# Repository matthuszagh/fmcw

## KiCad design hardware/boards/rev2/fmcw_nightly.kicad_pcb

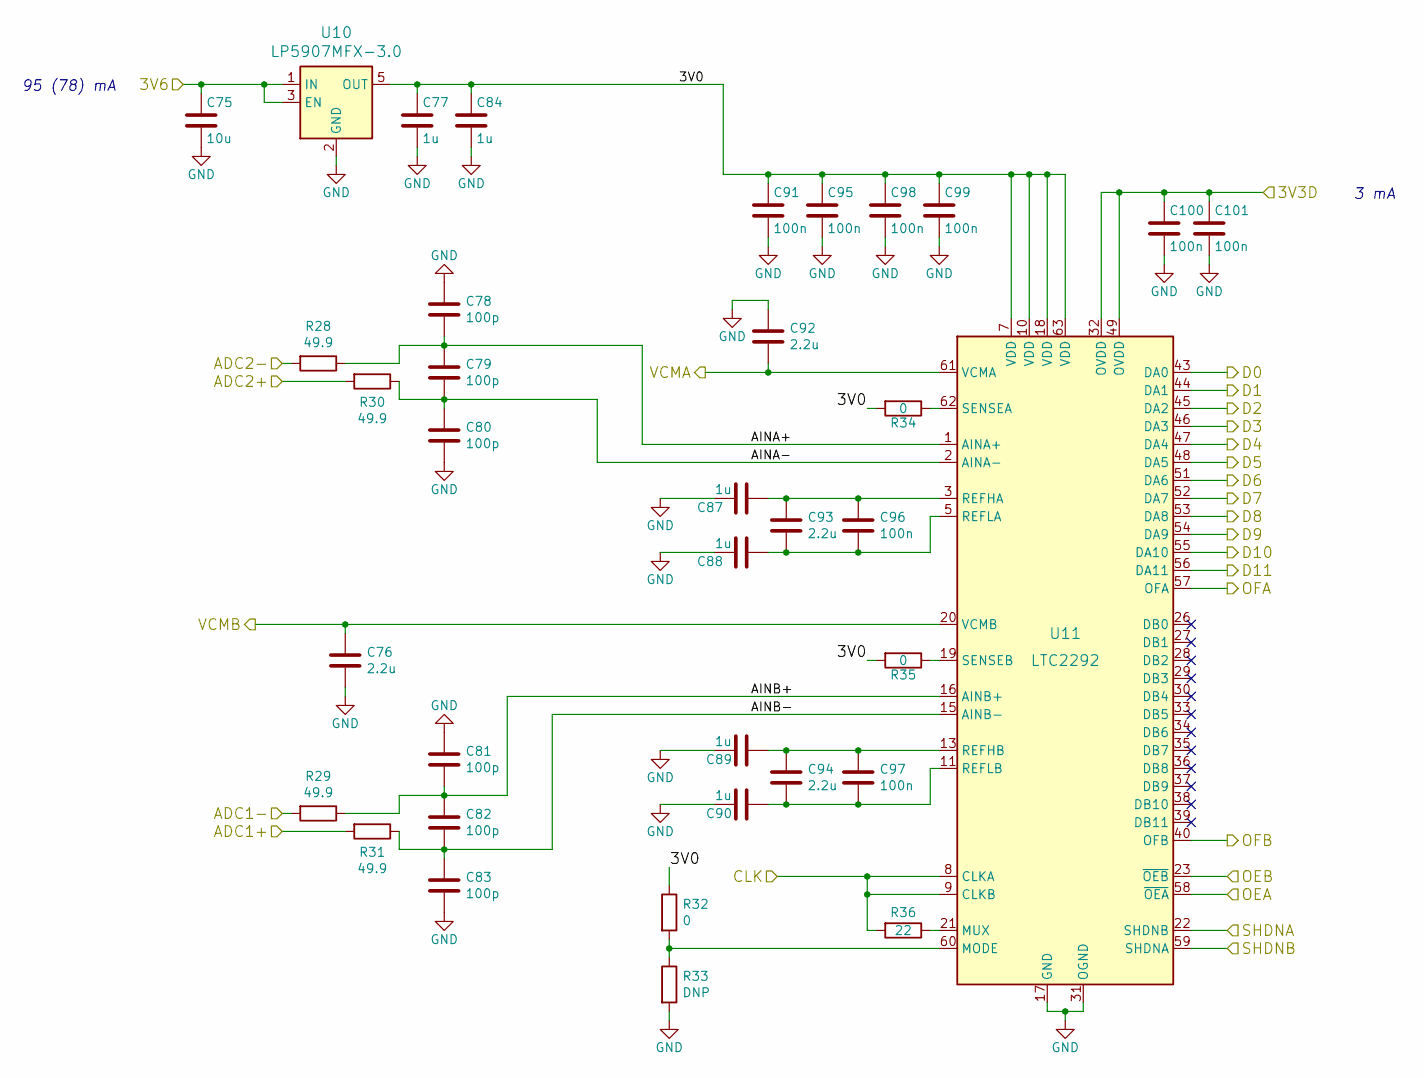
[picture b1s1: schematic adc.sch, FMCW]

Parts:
C75: 10u; C_0805_2012Metric
C76, C92, C93, C94: 2.2u; C_0603_1608Metric
C77, C84, C87, C88, C89, C90: 1u; C_0603_1608Metric
C78, C79, C80, C81, C82, C83: 100p; C_0402_1005Metric
C91, C95, C96, C97, C98, C99, C100, C101: 100n; C_0402_1005Metric
R28, R29, R30, R31: 49.9; R_0402_1005Metric
R32, R34, R35: 0; R_0402_1005Metric
R33: DNP; R_0402_1005Metric
R36: 22; R_0402_1005Metric
U10: LP5907MFX-3.0; SOT-23-5
U11: LTC2292; QFN-64-1EP_9x9mm_P0.5mm_EP7.15x7.15mm_ThermalVias

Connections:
/3V6: C75.1, U10.1 (IN), U10.3 (EN); also elsewhere on the board
/ADC1+: R31.2; also elsewhere on the board
/ADC1-: R29.2; also elsewhere on the board
/ADC2+: R30.2; also elsewhere on the board
/ADC2-: R28.2; also elsewhere on the board
/ADC_REF: R36.2, U11.8 (CLKA), U11.9 (CLKB); also elsewhere on the board
/ADC_VCM1: C92.2, U11.61 (VCMA); also elsewhere on the board
/ADC_VCM2: C76.1, U11.20 (VCMB); also elsewhere on the board
/fpga/ADC_OE1: U11.58 (~OEA); also elsewhere on the board
/fpga/ADC_OE2: U11.23 (~OEB); also elsewhere on the board
/fpga/ADC_SHDN1: U11.22 (SHDNB); also elsewhere on the board
/fpga/ADC_SHDN2: U11.59 (SHDNA); also elsewhere on the board
/fpga/D0: U11.43 (DA0); also elsewhere on the board
/fpga/D1: U11.44 (DA1); also elsewhere on the board
/fpga/D2: U11.45 (DA2); also elsewhere on the board
/fpga/D3: U11.46 (DA3); also elsewhere on the board
/fpga/D4: U11.47 (DA4); also elsewhere on the board
/fpga/D5: U11.48 (DA5); also elsewhere on the board
/fpga/D6: U11.51 (DA6); also elsewhere on the board
/fpga/D7: U11.52 (DA7); also elsewhere on the board
/fpga/D8: U11.53 (DA8); also elsewhere on the board
/fpga/D9: U11.54 (DA9); also elsewhere on the board
/fpga/D10: U11.55 (DA10); also elsewhere on the board
/fpga/D11: U11.56 (DA11); also elsewhere on the board
/fpga/OF1: U11.57 (OFA); also elsewhere on the board
/fpga/OF2: U11.40 (OFB); also elsewhere on the board
/fpga/adc/3V0: C77.1, C84.1, C91.1, C95.1, C98.1, C99.1, R32.1, R34.2, R35.2, U10.5 (OUT), U11.7 (VDD), U11.10 (VDD), U11.18 (VDD), U11.63 (VDD)
/fpga/adc/AINA+: C78.2, C79.1, R28.1, U11.1 (AINA+)
/fpga/adc/AINA-: C79.2, C80.1, R30.1, U11.2 (AINA-)
/fpga/adc/AINB+: C81.2, C82.1, R29.1, U11.16 (AINB+)
/fpga/adc/AINB-: C82.2, C83.1, R31.1, U11.15 (AINB-)
GND: C75.2, C76.2, C77.2, C78.1, C80.2, C81.1, C83.2, C84.2, C87.2, C88.2, C89.2, C90.2, C91.2, C92.1, C95.2, C98.2, C99.2, C100.2, C101.2, R33.2, U10.2 (GND), U11.17 (GND), U11.31 (OGND), U11.50 (OGND), U11.64 (GND), U11.65 (GND); also elsewhere on the board
unnamed: C87.1, C93.1, C96.1, U11.3 (REFHA), U11.4 (REFHA)
unnamed: C88.1, C93.2, C96.2, U11.5 (REFLA), U11.6 (REFLA)
unnamed: C89.1, C94.1, C97.1, U11.13 (REFHB), U11.14 (REFHB)
unnamed: C90.1, C94.2, C97.2, U11.11 (REFLB), U11.12 (REFLB)
unnamed: R32.2, R33.1, U11.60 (MODE)
unnamed: R34.1, U11.62 (SENSEA)
unnamed: R35.1, U11.19 (SENSEB)
unnamed: R36.1, U11.21 (MUX)

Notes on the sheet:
95 (78) mA
3 mA

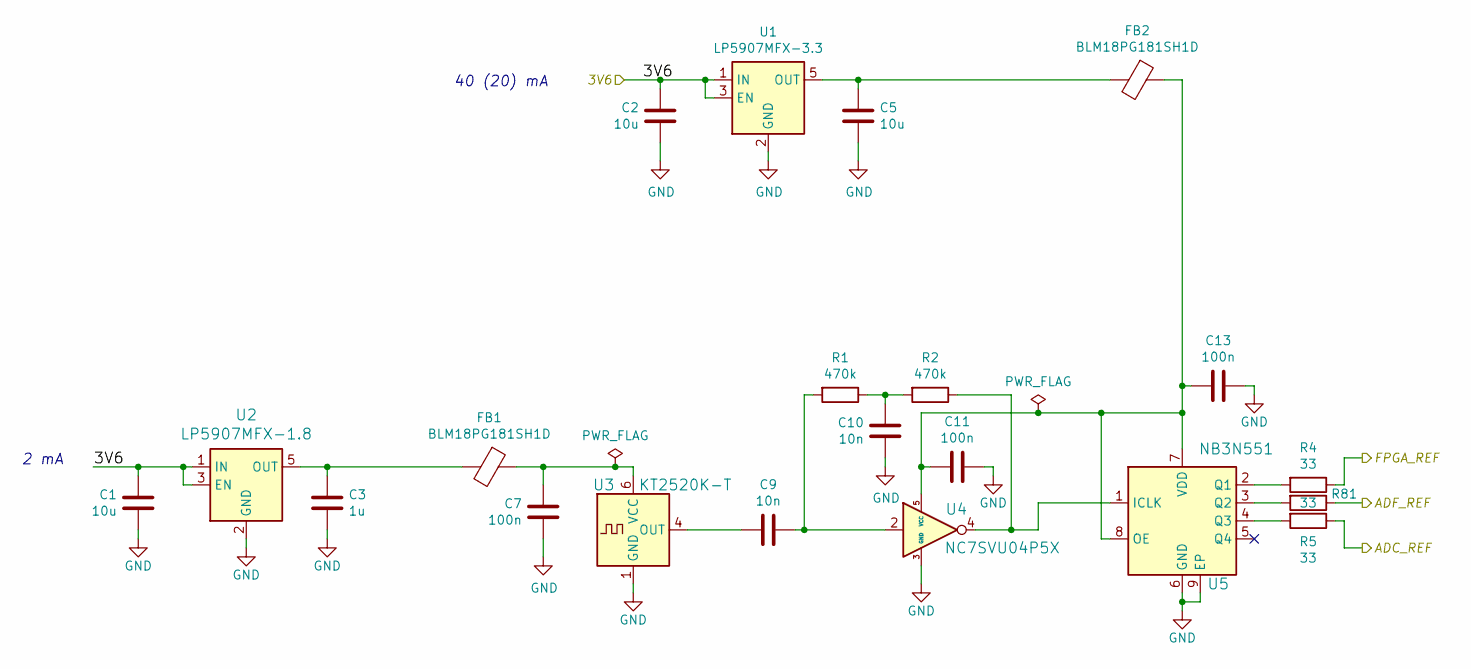
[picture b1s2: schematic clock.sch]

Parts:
C1, C2, C5: 10u; C_0805_2012Metric
C3: 1u; C_0805_2012Metric
C7, C11, C13: 100n; C_0402_1005Metric
C9, C10: 10n; C_0402_1005Metric
FB1, FB2: BLM18PG181SH1D; L_0603_1608Metric
R1, R2: 470k; R_0402_1005Metric
R4, R5, R81: 33; R_0402_1005Metric
U1: LP5907MFX-3.3; SOT-23-5
U2: LP5907MFX-1.8; SOT-23-5
U3: KT2520K-T; Oscillator_SMD_Kyocera_2520-6Pin_2.5x2.0mm
U4: NC7SVU04P5X; SOT-353_SC-70-5
U5: NB3N551; DFN-8-1EP_2x2mm_P0.5mm_EP0.9x1.3mm

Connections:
/3V6: C1.1, C2.1, U1.1 (IN), U1.3 (EN), U2.1 (IN), U2.3 (EN); also elsewhere on the board
/ADC_REF: R5.1; also elsewhere on the board
/ADF_REF: R81.1; also elsewhere on the board
/FPGA_REF: R4.1; also elsewhere on the board
GND: C1.2, C2.2, C3.2, C5.2, C7.1, C10.1, C11.1, C13.1, U1.2 (GND), U2.2 (GND), U3.1 (GND), U3.3 (GND), U4.3 (GND), U5.6 (GND), U5.9 (EP); also elsewhere on the board
unnamed: C3.1, FB1.2, U2.5 (OUT)
unnamed: C5.1, FB2.2, U1.5 (OUT)
unnamed: C7.2, FB1.1, U3.6 (VCC)
unnamed: C9.1, R1.2, U4.2
unnamed: C9.2, U3.4 (OUT)
unnamed: C10.2, R1.1, R2.2
unnamed: C11.2, C13.2, FB2.1, U4.5 (VCC), U5.7 (VDD), U5.8 (OE)
unnamed: R2.1, U4.4, U5.1 (ICLK)
unnamed: R4.2, U5.2 (Q1)
unnamed: R5.2, U5.4 (Q3)
unnamed: R81.2, U5.3 (Q2)

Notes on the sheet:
2 mA
40 (20) mA

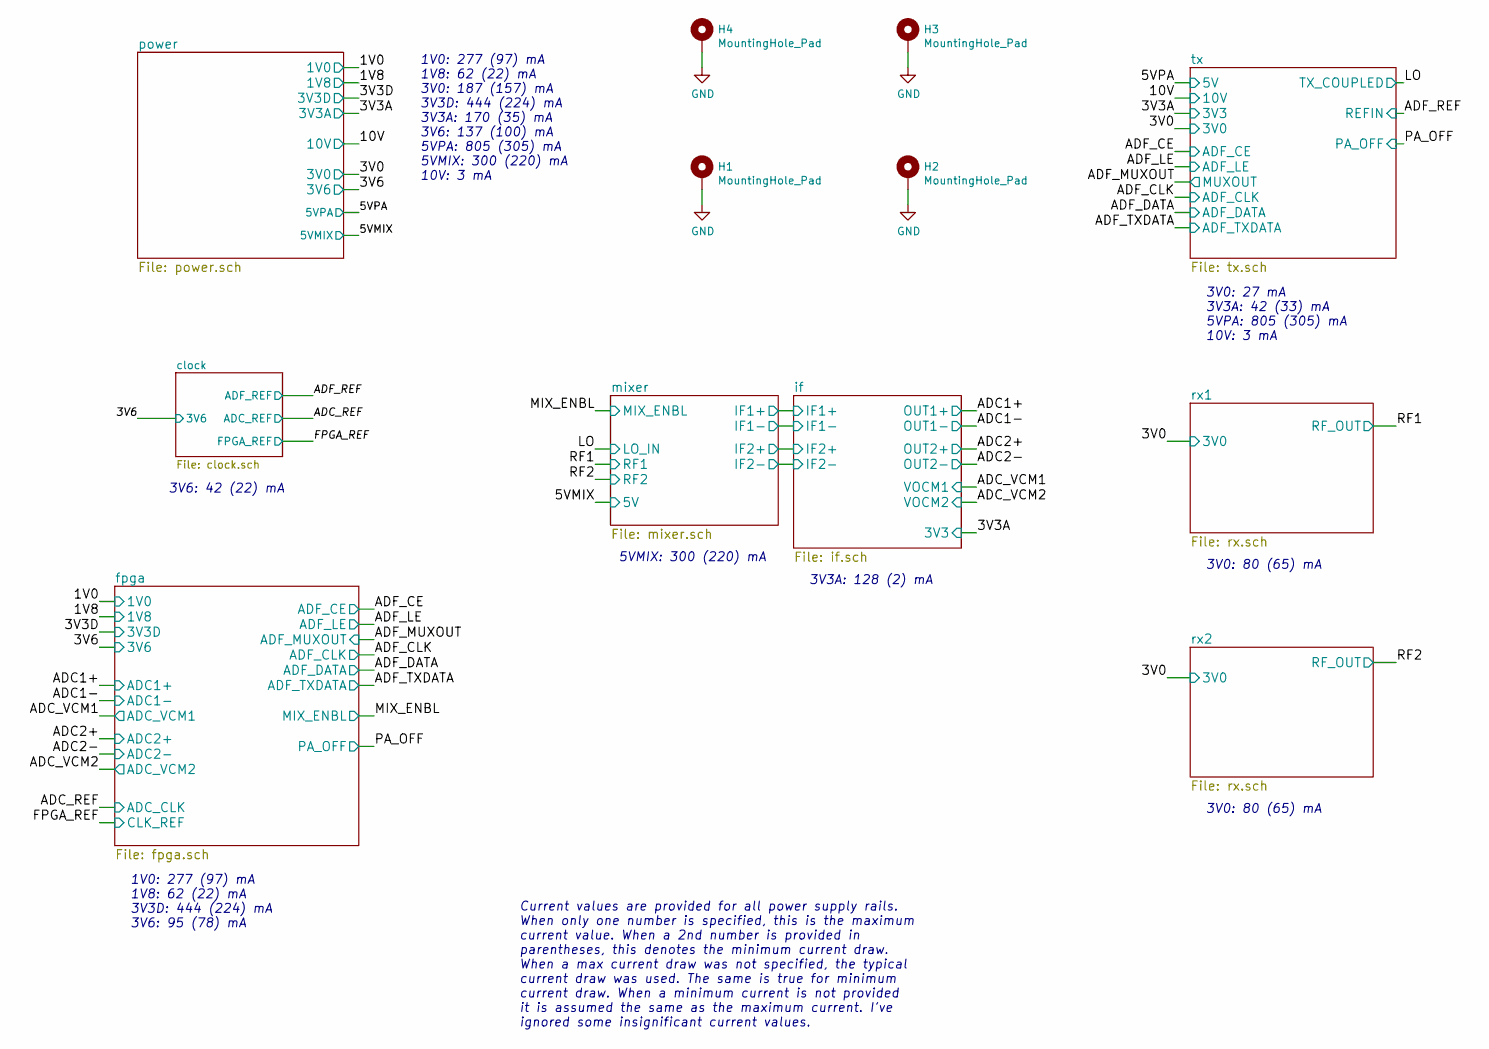
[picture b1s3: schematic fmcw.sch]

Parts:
H1, H2, H3, H4: MountingHole_Pad; MountingHole_3.2mm_M3_Pad_Via

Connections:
GND: H1.1, H2.1, H3.1, H4.1; also elsewhere on the board

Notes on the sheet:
1V0: 277 (97) mA 1V8: 62 (22) mA 3V3D: 444 (224) mA 3V6: 95 (78) mA
3V6: 42 (22) mA
1V0: 277 (97) mA 1V8: 62 (22) mA 3V0: 187 (157) mA 3V3D: 444 (224) mA 3V3A: 170 (35) mA 3V6: 137 (100) mA 5VPA: 805 (305) mA 5VMIX: 300 (220) mA 10V: 3 mA
Current values are provided for all power supply rails. When only one number is specified, this is the maximum current value. When a 2nd number is provided in parentheses, this denotes the minimum current draw. When a max current draw was not specified, the typical current draw was used. The same i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
5VMIX: 300 (220) mA
3V3A: 128 (2) mA
3V0: 27 mA 3V3A: 42 (33) mA 5VPA: 805 (305) mA 10V: 3 mA
3V0: 80 (65) mA

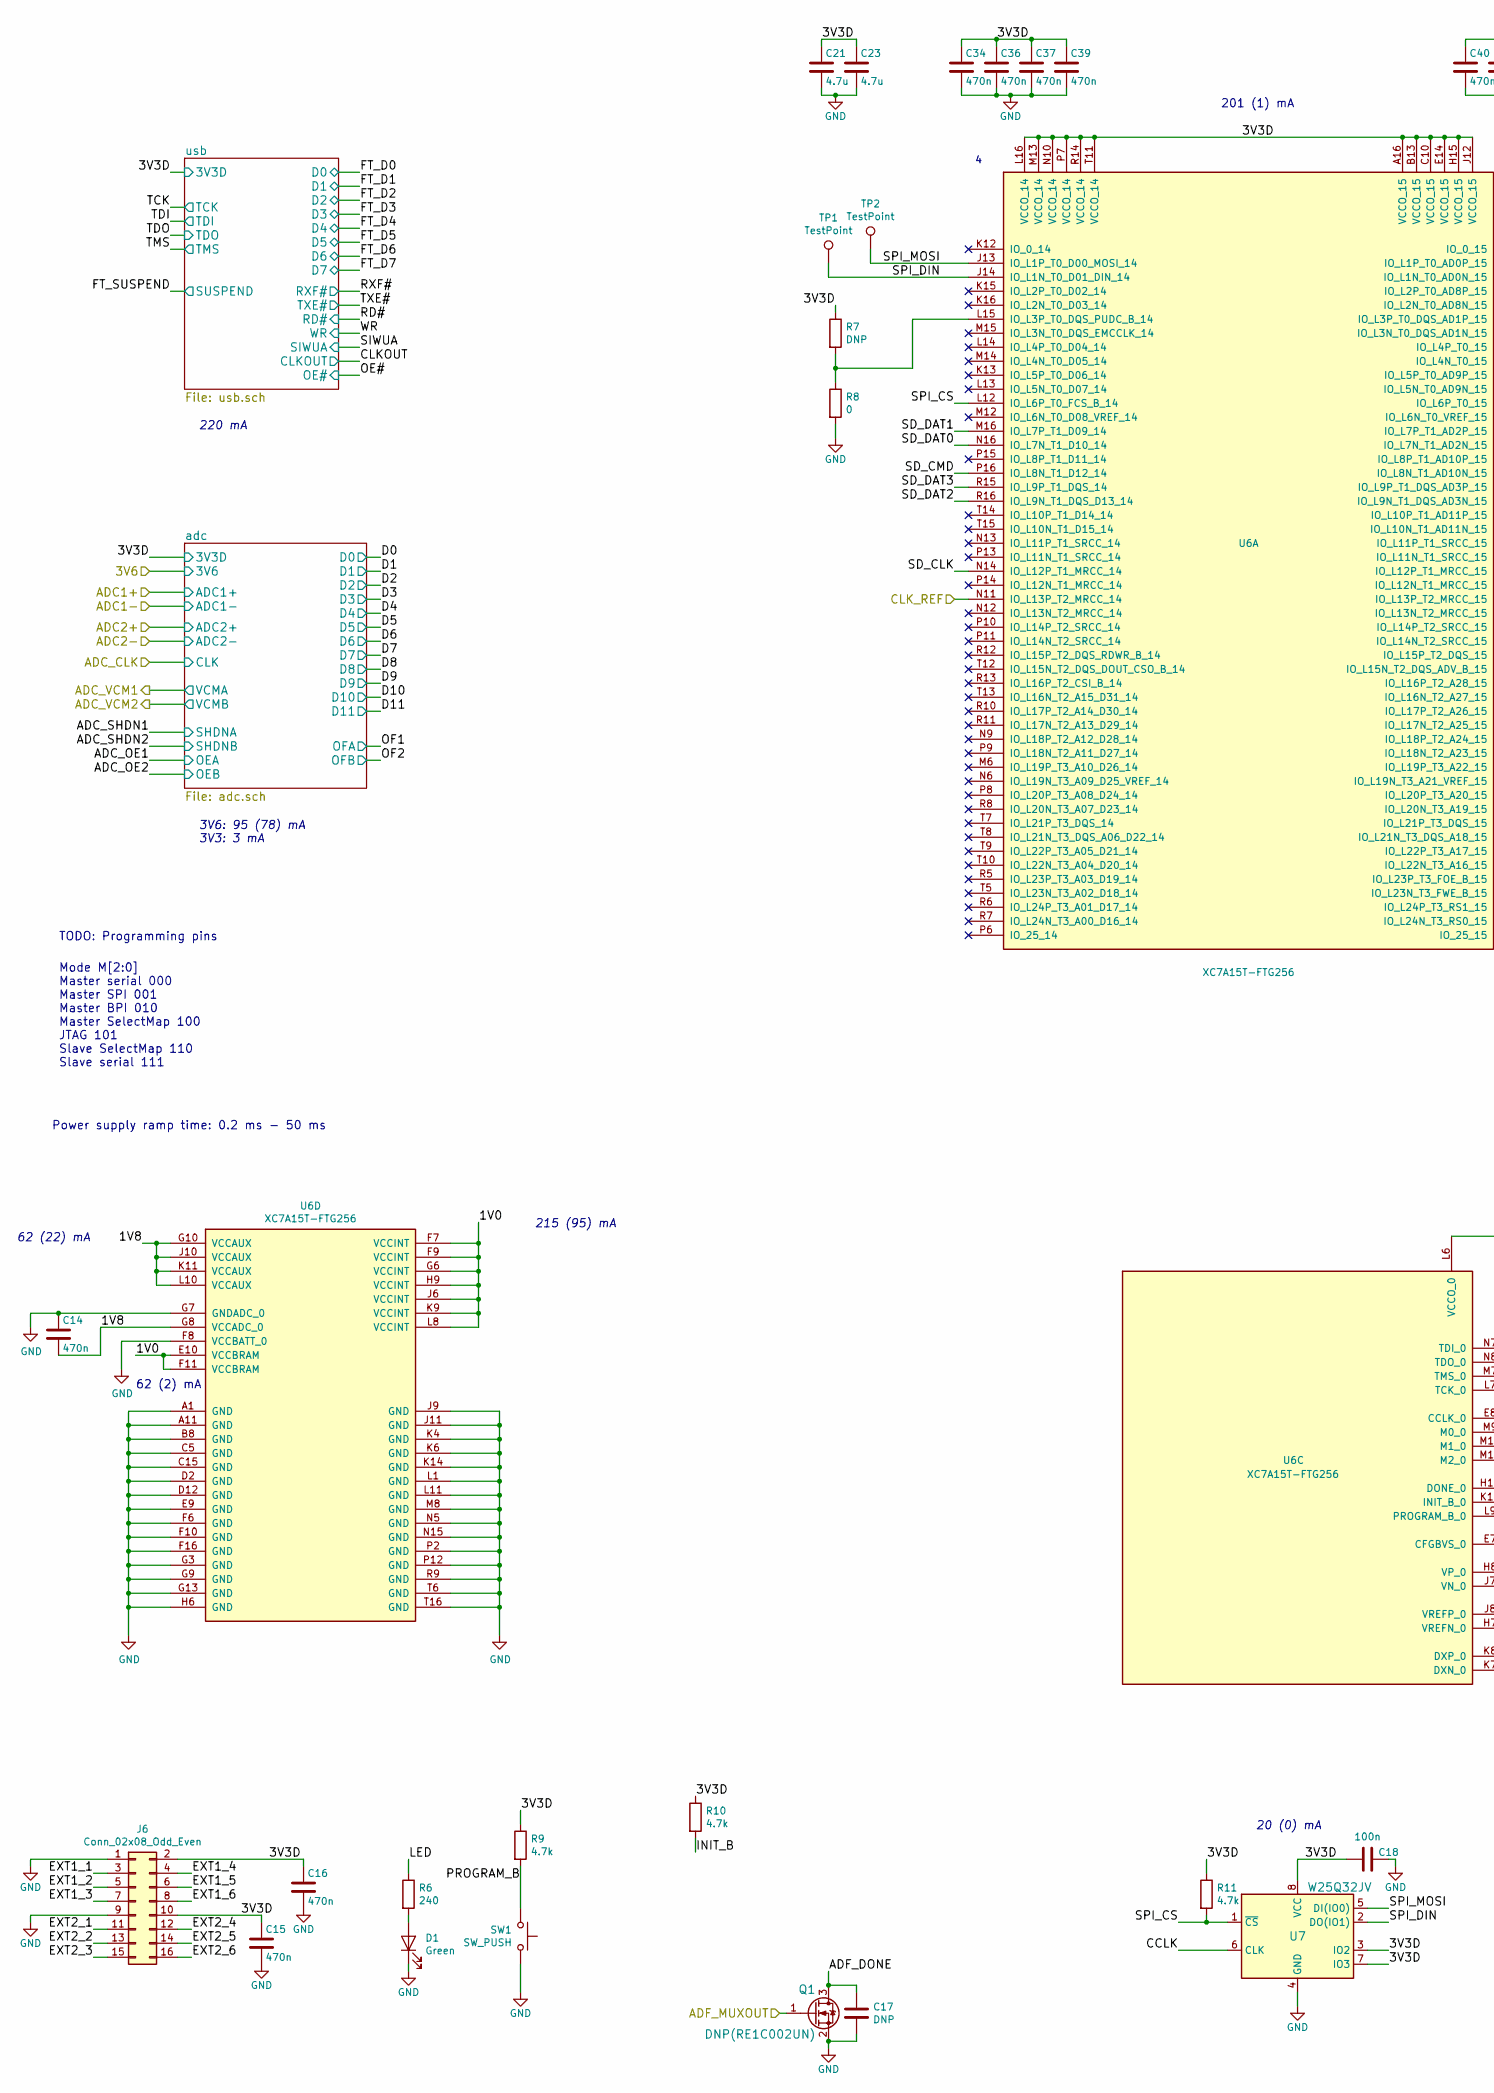
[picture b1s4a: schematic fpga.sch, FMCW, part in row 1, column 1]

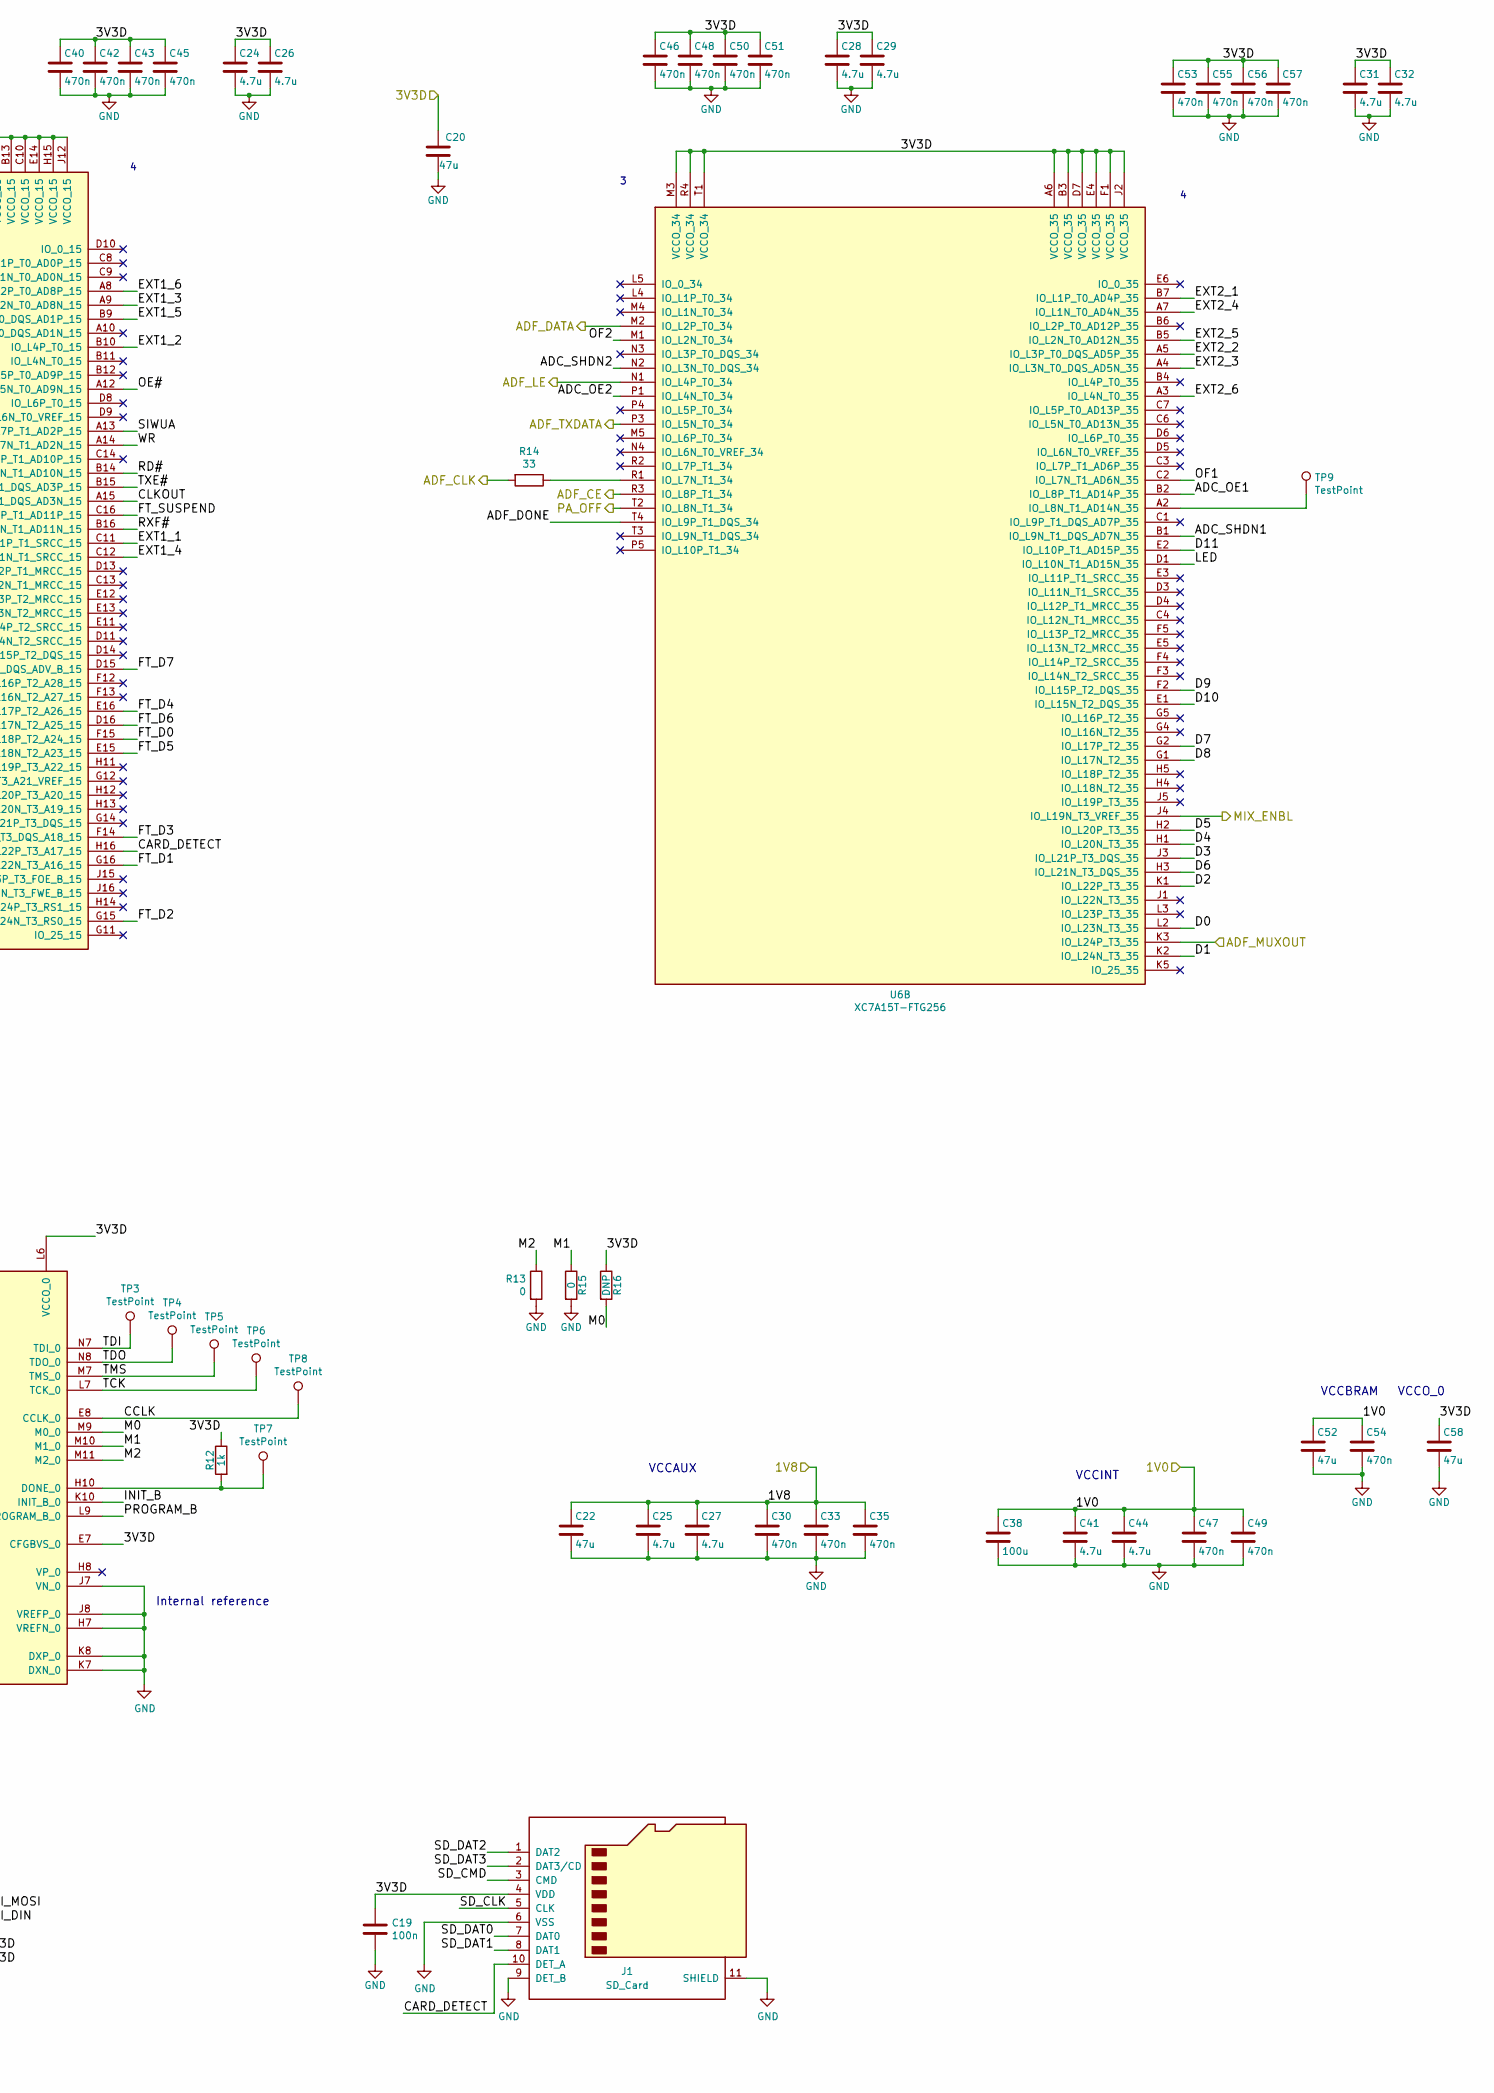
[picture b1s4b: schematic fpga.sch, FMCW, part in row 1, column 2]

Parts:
C14, C15, C16, C30, C33, C34, C35, C36, C37, C39, C40, C42, C43, C45, C46, C47, C48, C49, C50, C51, C53, C54, C55, C56, C57: 470n; C_0603_1608Metric
C17: DNP; C_0402_1005Metric
C18, C19: 100n; C_0402_1005Metric
C20, C22, C52, C58: 47u; C_1206_3216Metric
C21, C23, C24, C25, C26, C27, C28, C29, C31, C32, C41, C44: 4.7u; C_0805_2012Metric
C38: 100u; C_1210_3225Metric
D1: Green; LED_0603_1608Metric
J1: SD_Card; microSD_HC_Hirose_DM3BT-DSF-PEJS
J6: Conn_02x08_Odd_Even; PinHeader_2x08_P1.27mm_Vertical
Q1: DNP(RE1C002UN); SOT-416
R6: 240; R_0402_1005Metric
R7, R16: DNP; R_0402_1005Metric
R8, R13, R15: 0; R_0402_1005Metric
R9, R10, R11: 4.7k; R_0402_1005Metric
R12: 1k; R_0402_1005Metric
R14: 33; R_0402_1005Metric
SW1: SW_PUSH; SW_SPST_PTS810
TP1, TP2, TP3, TP4, TP5, TP6, TP7, TP8, TP9: TestPoint; TestPoint_Pad_D1.0mm
U6: XC7A15T-FTG256; Xilinx_FTG256
U7: W25Q32JV; SOIJ-8_5.3x5.3mm_P1.27mm

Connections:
/1V0: C38.1, C41.1, C44.1, C47.1, C49.1, C52.1, C54.1, U6.E10 (VCCBRAM), U6.F7 (VCCINT), U6.F9 (VCCINT), U6.F11 (VCCBRAM), U6.G6 (VCCINT), U6.H9 (VCCINT), U6.J6 (VCCINT), U6.K9 (VCCINT), U6.L8 (VCCINT); also elsewhere on the board
/1V8: C14.2, C22.1, C25.1, C27.1, C30.1, C33.1, C35.1, U6.G8 (VCCADC_0), U6.G10 (VCCAUX), U6.J10 (VCCAUX), U6.K11 (VCCAUX), U6.L10 (VCCAUX); also elsewhere on the board
/ADF_CE: U6.R3 (IO_L8P_T1_34); also elsewhere on the board
/ADF_CLK: R14.2; also elsewhere on the board
/ADF_DATA: U6.M2 (IO_L2P_T0_34); also elsewhere on the board
/ADF_LE: U6.N1 (IO_L4P_T0_34); also elsewhere on the board
/ADF_MUXOUT: Q1.1 (G), U6.K3 (IO_L24P_T3_35); also elsewhere on the board
/ADF_TXDATA: U6.P3 (IO_L5N_T0_34); also elsewhere on the board
/FPGA_REF: U6.N11 (IO_L13P_T2_MRCC_14); also elsewhere on the board
/MIX_ENBL: U6.J4 (IO_L19N_T3_VREF_35); also elsewhere on the board
/PA_OFF: U6.T2 (IO_L8N_T1_34); also elsewhere on the board
/fpga/ADC_OE1: U6.B2 (IO_L8P_T1_AD14P_35); also elsewhere on the board
/fpga/ADC_OE2: U6.P1 (IO_L4N_T0_34); also elsewhere on the board
/fpga/ADC_SHDN1: U6.B1 (IO_L9N_T1_DQS_AD7N_35); also elsewhere on the board
/fpga/ADC_SHDN2: U6.N2 (IO_L3N_T0_DQS_34); also elsewhere on the board
/fpga/ADF_DONE: C17.1, Q1.3 (D), U6.T4 (IO_L9P_T1_DQS_34)
/fpga/CARD_DETECT: J1.10 (DET_A), U6.H16 (IO_L22P_T3_A17_15)
/fpga/CCLK: TP8.1, U6.E8 (CCLK_0), U7.6 (CLK)
/fpga/CLKOUT: U6.A15 (IO_L9N_T1_DQS_AD3N_15); also elsewhere on the board
/fpga/D0: U6.L2 (IO_L23N_T3_35); also elsewhere on the board
/fpga/D1: U6.K2 (IO_L24N_T3_35); also elsewhere on the board
/fpga/D2: U6.K1 (IO_L22P_T3_35); also elsewhere on the board
/fpga/D3: U6.J3 (IO_L21P_T3_DQS_35); also elsewhere on the board
/fpga/D4: U6.H1 (IO_L20N_T3_35); also elsewhere on the board
/fpga/D5: U6.H2 (IO_L20P_T3_35); also elsewhere on the board
/fpga/D6: U6.H3 (IO_L21N_T3_DQS_35); also elsewhere on the board
/fpga/D7: U6.G2 (IO_L17P_T2_35); also elsewhere on the board
/fpga/D8: U6.G1 (IO_L17N_T2_35); also elsewhere on the board
/fpga/D9: U6.F2 (IO_L15P_T2_DQS_35); also elsewhere on the board
/fpga/D10: U6.E1 (IO_L15N_T2_DQS_35); also elsewhere on the board
/fpga/D11: U6.E2 (IO_L10P_T1_AD15P_35); also elsewhere on the board
/fpga/EXT1_1: J6.3, U6.C11 (IO_L11P_T1_SRCC_15)
/fpga/EXT1_2: J6.5, U6.B10 (IO_L4P_T0_15)
/fpga/EXT1_3: J6.7, U6.A9 (IO_L2N_T0_AD8N_15)
/fpga/EXT1_4: J6.4, U6.C12 (IO_L11N_T1_SRCC_15)
/fpga/EXT1_5: J6.6, U6.B9 (IO_L3P_T0_DQS_AD1P_15)
/fpga/EXT1_6: J6.8, U6.A8 (IO_L2P_T0_AD8P_15)
/fpga/EXT2_1: J6.11, U6.B7 (IO_L1P_T0_AD4P_35)
/fpga/EXT2_2: J6.13, U6.A5 (IO_L3P_T0_DQS_AD5P_35)
/fpga/EXT2_3: J6.15, U6.A4 (IO_L3N_T0_DQS_AD5N_35)
/fpga/EXT2_4: J6.12, U6.A7 (IO_L1N_T0_AD4N_35)
/fpga/EXT2_5: J6.14, U6.B5 (IO_L2N_T0_AD12N_35)
/fpga/EXT2_6: J6.16, U6.A3 (IO_L4N_T0_35)
/fpga/FT_D0: U6.F15 (IO_L18P_T2_A24_15); also elsewhere on the board
/fpga/FT_D1: U6.G16 (IO_L22N_T3_A16_15); also elsewhere on the board
/fpga/FT_D2: U6.G15 (IO_L24N_T3_RS0_15); also elsewhere on the board
/fpga/FT_D3: U6.F14 (IO_L21N_T3_DQS_A18_15); also elsewhere on the board
/fpga/FT_D4: U6.E16 (IO_L17P_T2_A26_15); also elsewhere on the board
/fpga/FT_D5: U6.E15 (IO_L18N_T2_A23_15); also elsewhere on the board
/fpga/FT_D6: U6.D16 (IO_L17N_T2_A25_15); also elsewhere on the board
/fpga/FT_D7: U6.D15 (IO_L15N_T2_DQS_ADV_B_15); also elsewhere on the board
/fpga/FT_SUSPEND: U6.C16 (IO_L10P_T1_AD11P_15); also elsewhere on the board
/fpga/INIT_B: R10.2, U6.K10 (INIT_B_0)
/fpga/LED: R6.1, U6.D1 (IO_L10N_T1_AD15N_35)
/fpga/M0: R16.2, U6.M9 (M0_0)
/fpga/M1: R15.1, U6.M10 (M1_0)
/fpga/M2: R13.1, U6.M11 (M2_0)
/fpga/OE#: U6.A12 (IO_L5N_T0_AD9N_15); also elsewhere on the board
/fpga/OF1: U6.C2 (IO_L7N_T1_AD6N_35); also elsewhere on the board
/fpga/OF2: U6.M1 (IO_L2N_T0_34); also elsewhere on the board
/fpga/PROGRAM_B: R9.2, SW1.1, U6.L9 (PROGRAM_B_0)
/fpga/RD#: U6.B14 (IO_L8N_T1_AD10N_15); also elsewhere on the board
/fpga/RXF#: U6.B16 (IO_L10N_T1_AD11N_15); also elsewhere on the board
/fpga/SD_CLK: J1.5 (CLK), U6.N14 (IO_L12P_T1_MRCC_14)
/fpga/SD_CMD: J1.3 (CMD), U6.P16 (IO_L8N_T1_D12_14)
/fpga/SD_DAT0: J1.7 (DAT0), U6.N16 (IO_L7N_T1_D10_14)
/fpga/SD_DAT1: J1.8 (DAT1), U6.M16 (IO_L7P_T1_D09_14)
/fpga/SD_DAT2: J1.1 (DAT2), U6.R16 (IO_L9N_T1_DQS_D13_14)
/fpga/SD_DAT3: J1.2 (DAT3/CD), U6.R15 (IO_L9P_T1_DQS_14)
/fpga/SIWUA: U6.A13 (IO_L7P_T1_AD2P_15); also elsewhere on the board
/fpga/SPI_CS: R11.2, U6.L12 (IO_L6P_T0_FCS_B_14), U7.1 (~CS)
/fpga/SPI_DIN: TP1.1, U6.J14 (IO_L1N_T0_D01_DIN_14), U7.2 (DO(IO1))
/fpga/SPI_MOSI: TP2.1, U6.J13 (IO_L1P_T0_D00_MOSI_14), U7.5 (DI(IO0))
/fpga/TCK: TP6.1, U6.L7 (TCK_0); also elsewhere on the board
/fpga/TDI: TP3.1, U6.N7 (TDI_0); also elsewhere on the board
/fpga/TDO: TP4.1, U6.N8 (TDO_0); also elsewhere on the board
/fpga/TMS: TP5.1, U6.M7 (TMS_0); also elsewhere on the board
/fpga/TXE#: U6.B15 (IO_L9P_T1_DQS_AD3P_15); also elsewhere on the board
/fpga/WR: U6.A14 (IO_L7N_T1_AD2N_15); also elsewhere on the board
GND: C14.1, C15.2, C16.2, C17.2, C18.1, C19.2, C20.2, C21.2, C22.2, C23.2, C24.2, C25.2, C26.2, C27.2, C28.2, C29.2, C30.2, C31.2, C32.2, C33.2, C34.2, C35.2, C36.2, C37.2, C38.2, C39.2, C40.2, C41.2, C42.2, C43.2, C44.2, C45.2, C46.2, C47.2, C48.2, C49.2, C50.2, C51.2, C52.2, C53.2, C54.2, C55.2, C56.2, C57.2, C58.2, D1.1 (K), J1.6 (VSS), J1.9 (DET_B), J1.11 (SHIELD), J6.1, J6.9, Q1.2 (S), R8.2, R13.2, R15.2, SW1.2, U6.A1 (GND), U6.A11 (GND), U6.B8 (GND), U6.C5 (GND), U6.C15 (GND), U6.D2 (GND), U6.D12 (GND), U6.E9 (GND), U6.F6 (GND), U6.F8 (VCCBATT_0), U6.F10 (GND), U6.F16 (GND), U6.G3 (GND), U6.G7 (GNDADC_0), U6.G9 (GND), U6.G13 (GND), U6.H6 (GND), U6.H7 (VREFN_0), U6.J7 (VN_0), U6.J8 (VREFP_0), U6.J9 (GND), U6.J11 (GND), U6.K4 (GND), U6.K6 (GND), U6.K7 (DXN_0), U6.K8 (DXP_0), U6.K14 (GND), U6.L1 (GND), U6.L11 (GND), U6.M8 (GND), U6.N5 (GND), U6.N15 (GND), U6.P2 (GND), U6.P12 (GND), U6.R9 (GND), U6.T6 (GND), U6.T16 (GND), U7.4 (GND); also elsewhere on the board
unnamed: D1.2 (A), R6.2
unnamed: R7.2, R8.1, U6.L15 (IO_L3P_T0_DQS_PUDC_B_14)
unnamed: R12.2, TP7.1, U6.H10 (DONE_0)
unnamed: R14.1, U6.R1 (IO_L7N_T1_34)
unnamed: TP9.1, U6.A2 (IO_L8N_T1_AD14N_35)

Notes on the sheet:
62 (22) mA
Power supply ramp time: 0.2 ms - 50 ms
TODO: Programming pins
Mode M[2:0] Master serial 000 Master SPI 001 Master BPI 010 Master SelectMap 100 JTAG 101 Slave SelectMap 110 Slave serial 111
62 (2) mA
220 mA
3V6: 95 (78) mA 3V3: 3 mA
215 (95) mA
201 (1) mA
20 (0) mA
Internal reference
VCCAUX
VCCINT
VCCBRAM
VCCO_0

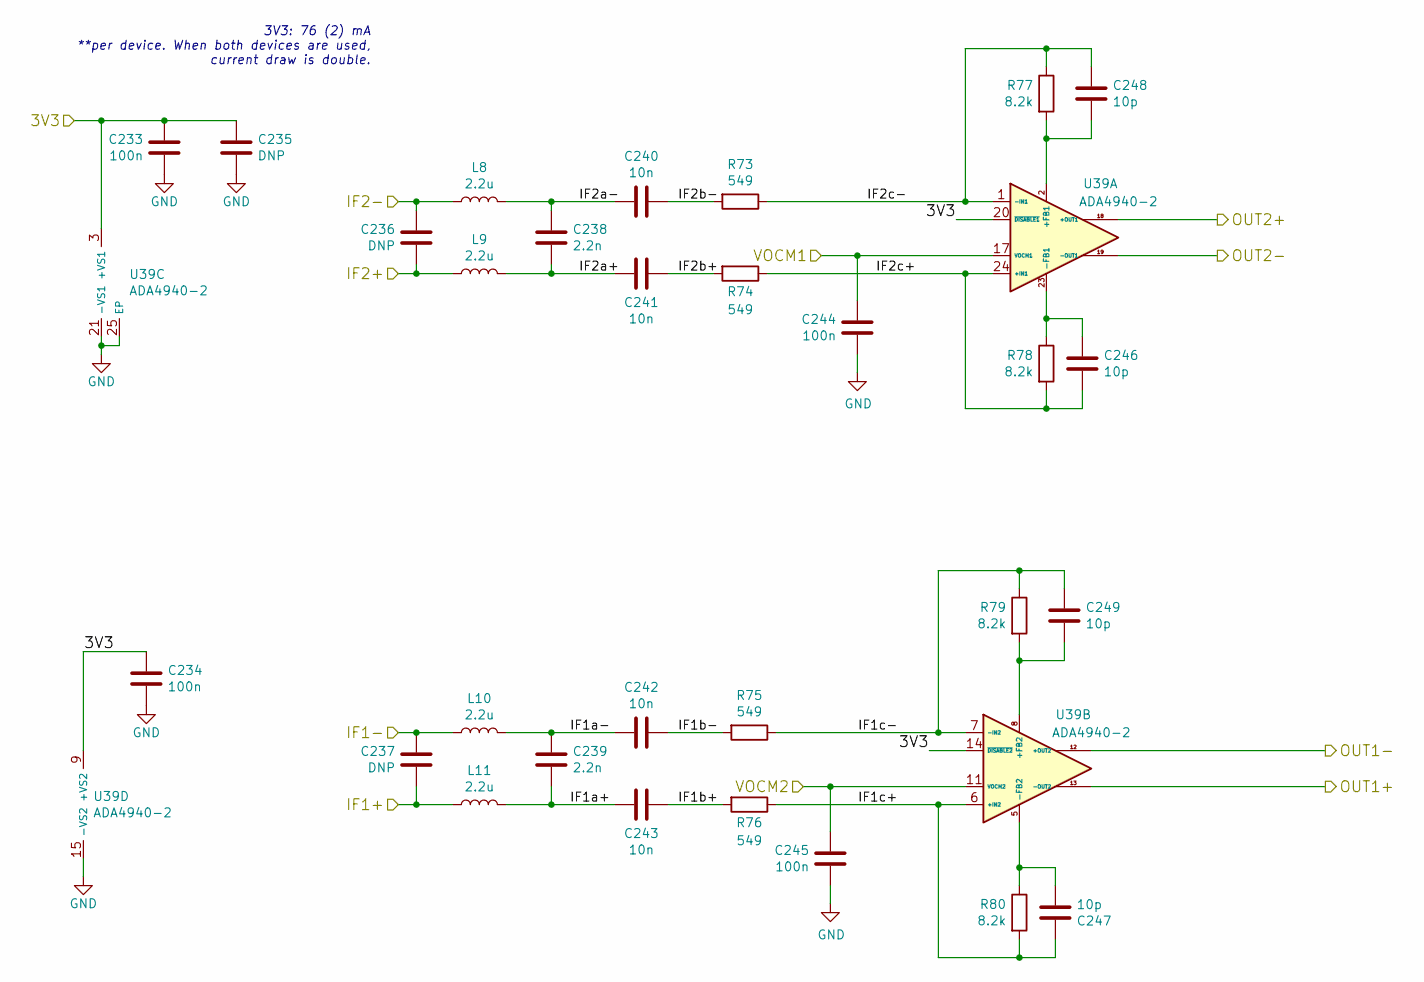
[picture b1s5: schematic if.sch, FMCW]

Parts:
C233, C234, C244, C245: 100n; C_0402_1005Metric
C235: DNP; C_0805_2012Metric
C236, C237: DNP; C_0402_1005Metric
C238, C239: 2.2n; C_0402_1005Metric
C240, C241, C242, C243: 10n; C_0402_1005Metric
C246, C247, C248, C249: 10p; C_0402_1005Metric
L8, L9, L10, L11: 2.2u; L_0603_1608Metric
R73, R74, R75, R76: 549; R_0402_1005Metric
R77, R78, R79, R80: 8.2k; R_0402_1005Metric
U39: ADA4940-2; LFCSP-24-1EP_4x4mm_P0.5mm_EP2.5x2.5mm_ThermalVias

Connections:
/3V3A: C233.1, C234.1, C235.1, U39.3 (+VS1), U39.4 (+VS1), U39.9 (+VS2), U39.10 (+VS2), U39.14 (~DISABLE2), U39.20 (~DISABLE1); also elsewhere on the board
/ADC1+: U39.13 (-OUT2); also elsewhere on the board
/ADC1-: U39.12 (+OUT2); also elsewhere on the board
/ADC2+: U39.18 (+OUT1); also elsewhere on the board
/ADC2-: U39.19 (-OUT1); also elsewhere on the board
/ADC_VCM1: C244.1, U39.17 (VOCM1); also elsewhere on the board
/ADC_VCM2: C245.1, U39.11 (VOCM2); also elsewhere on the board
/IF1+: C237.2, L11.1; also elsewhere on the board
/IF1-: C237.1, L10.1; also elsewhere on the board
/IF2+: C236.2, L9.1; also elsewhere on the board
/IF2-: C236.1, L8.1; also elsewhere on the board
/if/IF1a+: C239.2, C243.2, L11.2
/if/IF1a-: C239.1, C242.2, L10.2
/if/IF1b+: C243.1, R76.2
/if/IF1b-: C242.1, R75.2
/if/IF1c+: C247.1, R76.1, R80.2, U39.6 (+IN2)
/if/IF1c-: C249.1, R75.1, R79.1, U39.7 (-IN2)
/if/IF2a+: C238.2, C241.2, L9.2
/if/IF2a-: C238.1, C240.2, L8.2
/if/IF2b+: C241.1, R74.2
/if/IF2b-: C240.1, R73.2
/if/IF2c+: C246.2, R74.1, R78.2, U39.24 (+IN1)
/if/IF2c-: C248.1, R73.1, R77.1, U39.1 (-IN1)
GND: C233.2, C234.2, C235.2, C244.2, C245.2, U39.15 (-VS2), U39.16 (-VS2), U39.21 (-VS1), U39.22 (-VS1), U39.25 (EP); also elsewhere on the board
unnamed: C246.1, R78.1, U39.23 (-FB1)
unnamed: C247.2, R80.1, U39.5 (-FB2)
unnamed: C248.2, R77.2, U39.2 (+FB1)
unnamed: C249.2, R79.2, U39.8 (+FB2)

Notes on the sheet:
3V3: 76 (2) mA **per device. When both devices are used, current draw is double.
